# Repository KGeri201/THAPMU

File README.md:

<p align="center"></P>

# THAPMU
THAPMU stands for **T**emerature, **H**umiditity and **A**ir **P**ressure **M**easurement **U**nit. 

## Story
I wanted to create a small, cheap and easy to make IoT sensor, that works with nearly anything,  
to monitor the temerapture and humidity levels of multiple rooms.

## Hardware
The custom PCB is a very simple power adapter to power and connect the sensor and the ESP.

## Software
It uses [ESPHome](https://esphome.io/index.html), [MQTT](https://de.wikipedia.org/wiki/MQTT), [InfluxDB](https://www.influxdata.com/) and a [script](MQTTInfluxDBBridge.py) to connect all this together.  
I found a [code](https://randomnerdtutorials.com/esp8266-nodemcu-mqtt-publish-bme280-arduino/) very similar and nearly perfect for my use.  
I only modified it a little to make it a perfect fit.    
It uses Grafana to visualize the data, but anything else can be used.

## Installation
### Docker (recomended)
Follow the Guide for [docker deployment](DOCKER.md)

### Manual
Download the thapmu.sh with wget or any other way.
```sh
wget https://raw.githubusercontent.com/KGeri201/THAPMU/main/thapmu.sh
```
And execute it as sudo
```sh
sudo ./thapmu.sh
```
#### Step by step
Grafana will be added to apt sources.  
All the needed packages will be installed  
```sh
apt-get install -y influxdb influxdb-client mosquitto mosquitto-clients python3 python3-pip grafana-enterprise
```
All the neded files will be downloaded.
```sh
wget -q -O /tmp/requirements.txt https://raw.githubusercontent.com/KGeri201/THAPMU/main/requirements.txt
wget -q -O MQTTInfluxDBBridge.py https://raw.githubusercontent.com/KGeri201/THAPMU/main/MQTTInfluxDBBridge.py
wget -q -O /etc/systemd/system/mqttinfluxdbbridge.service https://raw.githubusercontent.com/KGeri201/THAPMU/main/mqttinfluxdbbridge.service
```
Additional config will be added to mosquitto  
```sh
echo "listener 1883" > /etc/mosquitto/conf.d/allow.conf && echo "allow_anonymous true" >> /etc/mosquitto/conf.d/allow.conf
```
Python libraries will also be installed  
```sh
pip3 -q install -r /tmp/requirements.txt
```
Database will be set up, and services will be started
```sh
systemctl start mqttinfluxdbbridge
systemctl start grafana-server
systemctl restart influxdb
systemctl start mosquitto
```
Additionaly you can also enable all the services to start automatically after starting the device  
```sh
systemctl enable mosquitto
systemctl enable influxdb
systemctl enable grafana-server
systemctl enable mqttinfluxdbbridge
```

## Sensor
### Requirements
* 1 THAPMU board (fully fitted, and ready to use)
* 1 ESP01 breakout board
* 1 BME or BMP sensor
* an extra external serial adapter to flash your ESP
* an USB-C cable to power the board.

### Instructions
#### ESPHome
1. Install ESPHome on a server.
2. Go to http://ip-of-your-server:6052
3. Add new device.
4. Load the [example_esphome.conf](example_esphome.conf) and edit the values to fit your needs.  
   Make sure that the right sensor is selected and all the credentials are right.
5. Flash the code to the ESP following the guide from ESPHome

#### Legacy
1. Open the code for the ESP and change the library according to your sensor.  
```ino
#include <Adafruit_BME280.h>

// Sensor I2C
Adafruit_BME280 sensor;
```
2. Fill in your WLAN SSID and password, and the address of the MQTT broker.  
   If your MQTT broker needs credentials to authenticate, set them.  
   Also add the location and the name of the device.
```ino
#define NAME "NAME_OF_THE_DEVICE"
#define LOCATION "LOCATION_OF_THE_DEVICE"
#define WIFI_SSID "REPLACE_WITH_YOUR_SSID"
#define WIFI_PASSWORD "REPLACE_WITH_YOUR_PASSWORD"

// Raspberri Pi Mosquitto MQTT Broker
#define MQTT_HOST IPAddress(X, X, X, X)
// For a cloud MQTT broker, type the domain name
//#define MQTT_HOST "example.com"
#define MQTT_PORT 1883
// If your MQTT broker requires authentication, set them below
#define MQTT_USER ""
#define MQTT_PASSWORD ""
``` 
3. Flash the ESP.  
4. Plug the board in somewhere and wait for it to connect to your WLAN and to the Server, which you previously set up (decribed under [Installation](https://github.com/KGeri201/THAPMU#installation)).
5. Go to the [Grafana](https://grafana.com/) site, hosted on your server http://ip-of-your-server:3000 and login with the default credentials.
6. Under the Configurations add the [InfluxDB](https://www.influxdata.com/products/influxdb-overview/) data source.  
  Fill in the name of the database, user and password.  
  These you have set during the setup process.
7. Make a new dashboard with the newly added InfluxDB datasource and choose the measurement.  
There are three topics:  
   - THAPMU/**LOCATION**/**NAME**/sensor/temperature/state   
   - THAPMU/**LOCATION**/**NAME**/sensor/humidity/state
   - THAPMU/**LOCATION**/**NAME**/sensor/pressure/state
8. You are up and running.  

## Credits
[HimbeersaftLP](https://github.com/HimbeersaftLP)  
[KGeri201](https://github.com/KGeri201)  

## License
[Apache License 2.0](LICENSE)

## Project status
Ready to deploy.

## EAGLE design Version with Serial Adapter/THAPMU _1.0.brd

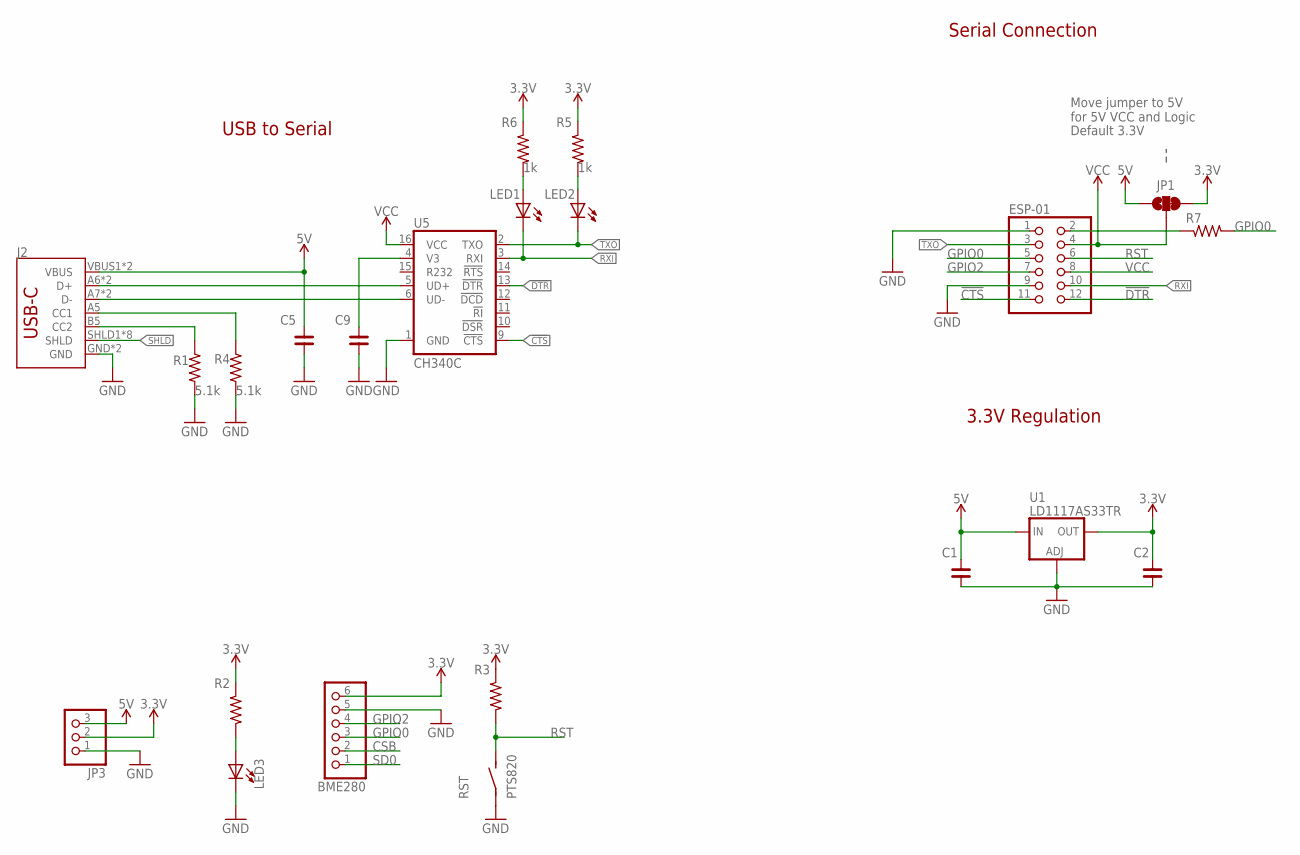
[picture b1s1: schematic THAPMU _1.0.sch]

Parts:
BME280: PINHD-1X6; 1X06
C1, C5: 0.1uF; C1206
C2: 10uF; C1206
C9: 10nF; C1206
ESP-01: PINHD-2X6; 2X06
J2: USB_C16PIN; USB-C-16P
JP1: JUMPER-SMT_3_1-NC_TRACE_SILK; SMT-JUMPER_3_1-NC_TRACE_SILK
JP3: PINHD-1X3_2.00; 1X03M
LED1: GREEN; 1206
LED2: Yellow; 1206
LED3: BLUE; 1206
R1, R4: 5.1k; R1206
R2, R3, R5, R6, R7: 1k; R1206
RST: PTS820
U1: LD1117AS33TR; SOT223
U5: CH340C; SO016

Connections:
3.3V: BME280.6, C2.1, JP1.3, JP3.2, R2.2, R3.2, R5.2, R6.2, U1.4 (OUT)
5V: C1.1, C5.1, J2.VBUS1 (VBUS), J2.VBUS2 (VBUS), JP1.1, JP3.3, U1.3 (IN)
!CTS: ESP-01.11, U5.9 (!CTS)
!DTR: ESP-01.12, U5.13 (!DTR)
CC1: J2.A5 (CC1), R4.2
CC2: J2.B5 (CC2), R1.2
CSB: BME280.2
D+: J2.A6 (D+), J2.B6 (D+), U5.5 (UD+)
D-: J2.A7 (D-), J2.B7 (D-), U5.6 (UD-)
GND: BME280.5, C1.2, C2.2, C5.2, C9.2, ESP-01.1, ESP-01.9, J2.GND, J2.GND2 (GND), JP3.1, LED3.C, R1.1, R4.1, RST.1, U1.1 (ADJ), U5.1 (GND)
GPIO0: BME280.3, ESP-01.5, R7.2
GPIO2: BME280.4, ESP-01.7
unnamed: C9.1, U5.4 (V3)
unnamed: LED3.A, R2.1
unnamed: ESP-01.2, R7.1
unnamed: LED1.A, R6.1
unnamed: LED2.A, R5.1
RST: ESP-01.6, R3.1, RST.2 (S)
RXI: ESP-01.10, LED1.C, U5.3 (RXI)
SD0: BME280.1
SHLD: J2.SHLD1 (SHLD), J2.SHLD2 (SHLD), J2.SHLD3 (SHLD), J2.SHLD4 (SHLD), J2.SHLD5 (SHLD), J2.SHLD6 (SHLD), J2.SHLD7 (SHLD), J2.SHLD8 (SHLD)
TXO: ESP-01.3, LED2.C, U5.2 (TXO)
VCC: ESP-01.4, ESP-01.8, JP1.2, U5.16 (VCC)

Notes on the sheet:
Default 3.3V
USB to Serial
3.3V Regulation
Move jumper to 5V for 5V VCC and Logic
Serial Connection

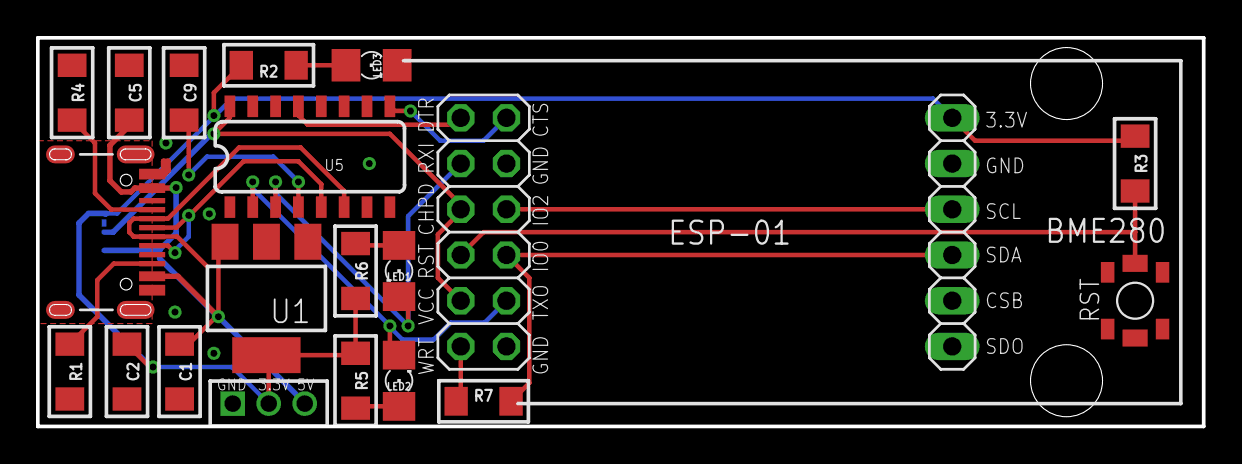
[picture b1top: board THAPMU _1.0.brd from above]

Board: 2 copper layers, 64.8 x 21.6 mm, 23 parts (1 on the bottom side), 21 nets.

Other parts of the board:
U$1: THAPMU

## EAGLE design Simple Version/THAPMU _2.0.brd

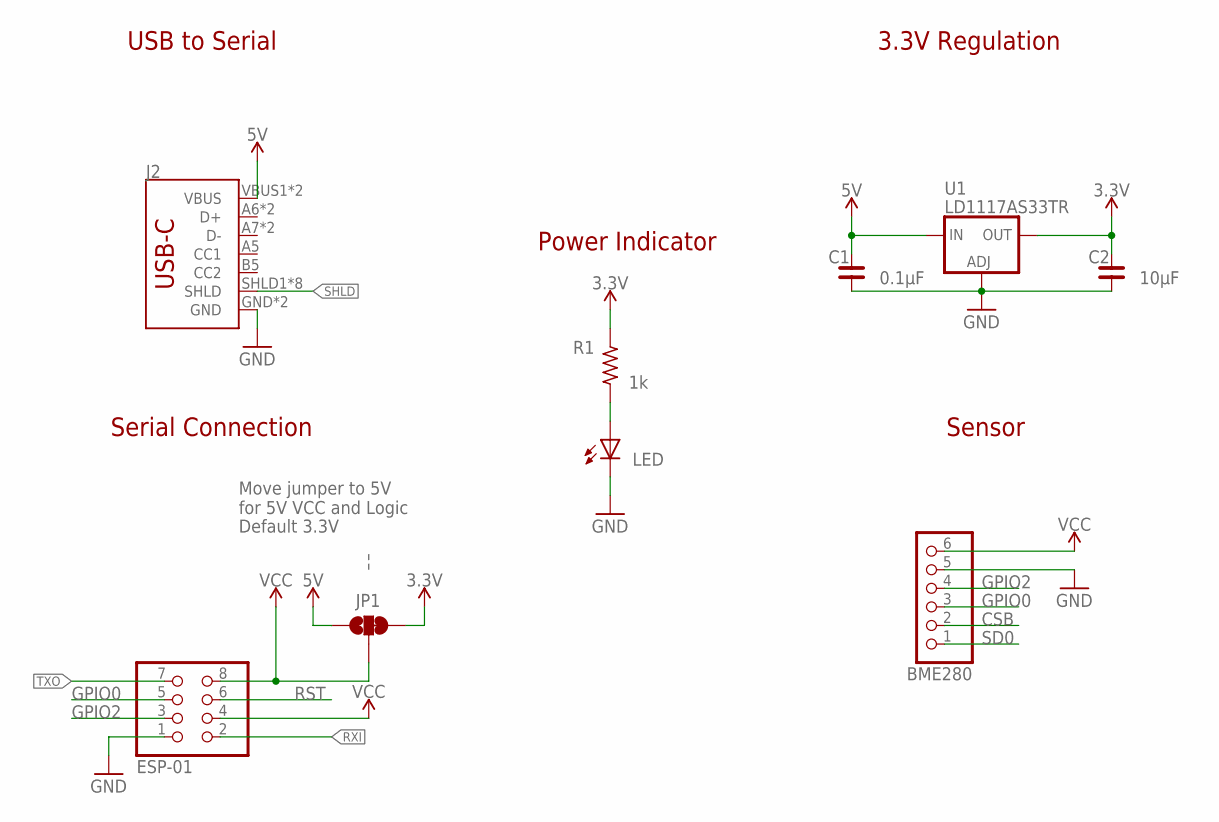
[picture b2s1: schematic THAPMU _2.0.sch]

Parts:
BME280: PINHD-1X6; 1X06
C1: 0.1µF; C1206
C2: 10µF; C1206
ESP-01: PINHD-2X4; 2X04
J2: USB_C16PIN; USB-C-16P
JP1: JUMPER-SMT_3_1-NC_TRACE_SILK; SMT-JUMPER_3_1-NC_TRACE_SILK
LED: LEDSMT1206; 1206
R1: 1k; R1206
U1: LD1117AS33TR; SOT223

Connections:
3.3V: C2.2, JP1.3, R1.2, U1.4 (OUT)
5V: C1.2, J2.VBUS1 (VBUS), J2.VBUS2 (VBUS), JP1.1, U1.3 (IN)
CSB: BME280.2
GND: BME280.5, C1.1, C2.1, ESP-01.1, J2.GND, J2.GND2 (GND), LED.C, U1.1 (ADJ)
GPIO0: BME280.3, ESP-01.5
GPIO2: BME280.4, ESP-01.3
unnamed: LED.A, R1.1
RST: ESP-01.6
RXI: ESP-01.2
SD0: BME280.1
SHLD: J2.SHLD1 (SHLD), J2.SHLD2 (SHLD), J2.SHLD3 (SHLD), J2.SHLD4 (SHLD), J2.SHLD5 (SHLD), J2.SHLD6 (SHLD), J2.SHLD7 (SHLD), J2.SHLD8 (SHLD)
TXO: ESP-01.7
VCC: BME280.6, ESP-01.4, ESP-01.8, JP1.2

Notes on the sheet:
Default 3.3V
USB to Serial
3.3V Regulation
Move jumper to 5V for 5V VCC and Logic
Serial Connection
Sensor
Power Indicator

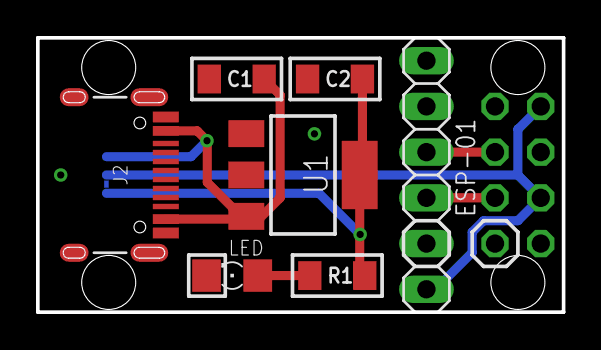
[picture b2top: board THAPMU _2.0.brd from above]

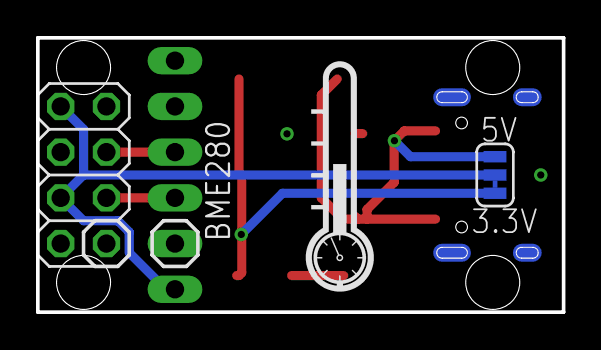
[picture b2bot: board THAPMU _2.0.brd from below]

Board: 2 copper layers, 29.2 x 15.2 mm, 10 parts (2 on the bottom side), 8 nets.

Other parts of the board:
LOGO: THAPMU

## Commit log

2021-07-20 Create test
2021-07-20 Rename ThermoAndHumidityMeter _1.0.brd to THAPMU _1.0.brd
2021-07-20 Rename ThermoAndHumidityMeter _1.0.sch to THAPMU _1.0.sch
2021-07-20 Create foo
2021-07-20 Rename Simple version/THAPMU _1.0.brd to Version with Serial Adapter/THAPMU _1.0.brd
2021-07-20 Rename Simple version/THAPMU _1.0.sch to Version with Serial Adapter/THAPMU _1.0.sch
2021-07-20 Rename Version with serial adapter/THAPMU _1.0.brd to Simple Version/THAPMU _1.0.brd
2021-07-20 Rename Version with serial adapter/THAPMU _1.0.sch to Simple Version/THAPMU _1.0.sch
2021-08-05 minor fixes
2022-09-23 added sampling
2022-09-24 Create Dockerfile
2022-09-24 Update Dockerfile
2022-09-24 added docker-compose.yml
2022-09-24 changed alpine to debian
2022-09-24 updated setup
2022-09-25 updated Dockerfile
2022-09-25 added backup and restore
2022-09-27 remade logo
2022-09-29 Rename THAPMU _1.0.brd to THAPMU _2.0.brd
2022-09-29 Rename THAPMU _1.0.sch to THAPMU _2.0.sch
2022-09-30 updated setup, due to not functional setup inside docker
2022-10-02 updated setup, added mqtt authentification
2022-10-02 made use of mqtt auth easier
2022-10-02 Create LICENSE
2022-10-02 renamed setup.sh to thapmu.sh
2022-10-02 updated setup script
2022-10-10 removed sampling
2023-08-05 Create example_esphome.conf
    added esample configuration for ESP Home compatibility
2023-08-31 cleaned up docker
2024-08-10 changed docker registry
2025-01-16 fixed paho.mqtt.client issues
2025-01-16 added latest tag to docker

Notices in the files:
parts and their libraries:
SparkFun-Connectors: Licensing: Creative Commons ShareAlike 4.0 International - https://creativecommons.org/licenses/by-sa/4.0
rc-master-smd: Copyright (C) 2007, Bob Starr
switch-ck: Creative Commons Attribution-ShareAlike 4.0 International
